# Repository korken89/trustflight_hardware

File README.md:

# ThrustFlight hardware reference design

A small and simple flight controller to be used with the  [trustflight firmware](https://github.com/korken89/trustflight_firmware) flight controller firmware, which is focusing on safety by using the Rust programming language.

## License

The hardware is OSHW using the Cern-OHL license.

## Images

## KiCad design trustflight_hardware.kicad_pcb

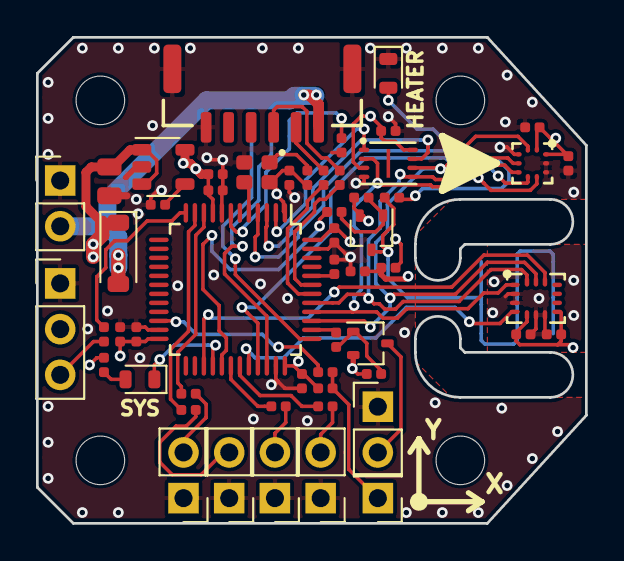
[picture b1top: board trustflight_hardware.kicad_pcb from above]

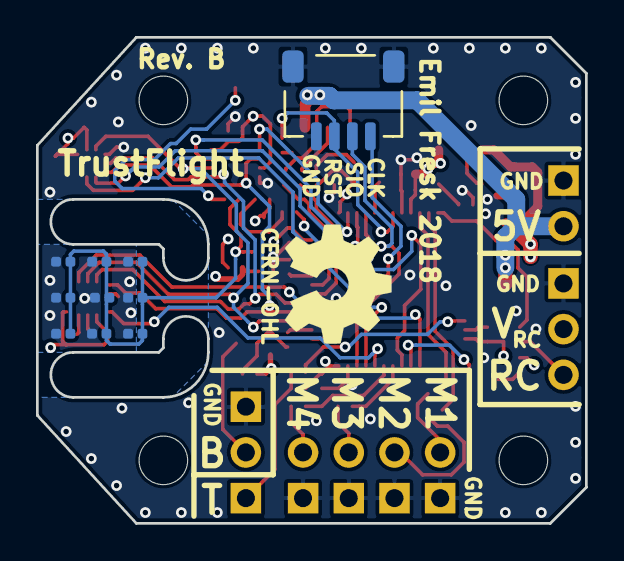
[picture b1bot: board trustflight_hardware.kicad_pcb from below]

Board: 4 copper layers, 30.5 x 27.0 mm, 69 parts (11 on the bottom side), 46 nets.

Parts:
C1, C2, C3, C4, C5, C7, C10, C12, C13, C14, C15, C16: 100n; C_0402_1005Metric_Rounded
C6: 22u; C_0805
C8, C9, C11: 4.7u; C_0402_1005Metric_Rounded
D1: LED_RED; D_0603_1608Metric_Rounded
D2: PMEG4005EGWX; D_SOD-123
D3: LED_BLUE; D_0603_1608Metric_Rounded
J1, J2, J3, J4, J6, J7: Conn_01x02; PinHeader_1x02_P2.54mm_Vertical
J5: Conn_01x01; PinHeader_1x01_P2.54mm_Vertical
J8: Conn_01x03; PinHeader_1x03_P2.54mm_Vertical
J9: swd-4; jst-sh-hor-4
J10: Dronecode_Telemetry; SM06B-GHS-TB
L1: MAF1005GAD352AT000; R_0402_1005Metric_Rounded
LOGO1: Logo_Open_Hardware_Small; OSHW-Symbol_6.7x6mm_SilkScreen
MK1, MK2, MK3, MK4: Mounting_Hole; MountingHole_2.7mm_M2.5
Q1, Q2: DMG1013UW; SOT-323_SC-70
R1, R2, R3, R4, R5, R12, R19, R21, R22, R23: 100; R_0402_1005Metric_Rounded
R6, R11: 1k; R_0402_1005Metric_Rounded
R7, R20, R24, R26: 10k; R_0402_1005Metric_Rounded
R8, R9, R10, R13, R14, R15, R16, R17, R18, R25: 180; R_0402_1005Metric_Rounded
U1: W25X40CLUXIG; USON-8-3x2mm-EP
U2: ISM330DLC; LGA-14-2.5x3
U3: BMP388; HLGA-10L-2.0x2.0-BMP388
U4: STM32F302CBT6; LQFP-48_7x7mm_Pitch0.5mm
U5: MIC5318-3.3YD5; SOT-23-5
X1: SIT8008BI-71-33S-16.000000G; Crystal_4Pin_2.0x1.6mm

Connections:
+3V3: C5.1, C9.1, C10.2, C11.1, C12.1, C13.1, C14.1, C16.1, L1.2, R11.2, R24.1, U1.3, U1.8, U4.1, U4.9, U4.24, U4.36, U4.48, U5.5, X1.4
+5V: D2.2, J6.2, J10.1
/BAR_CS: U3.6, U4.4
/BAR_INT: U3.7, U4.33
/BOOT0: R26.1, U4.44
/BUZZER: R23.2, U4.38
/BUZZ_P: J7.2, Q2.3
/CLK: U4.5, X1.3
/COM_RX: R22.2, U4.43
/COM_TX: R21.2, U4.42
/ESC_TLM: R12.2, U4.22
/ESC_TLM_P: J5.1, R11.1, R12.1
/F.port: R19.2, U4.12
/F.port_P: J8.3, R19.1
/FLASH_CS: U1.1, U4.2
/FLASH_HOLD: U1.7, U4.3
/HEATER: R1.2, U4.29
/IMU_CS: U2.12, U4.27
/IMU_INT: U2.4, U4.32
/LED: D3.1, U4.28
/M1: R2.2, U4.10
/M1_P: J1.2, R2.1
/M2: R3.2, U4.11
/M2_P: J2.2, R3.1
/M3: R4.2, U4.30
/M3_P: J3.2, R4.1
/M4: R5.2, U4.31
/M4_P: J4.2, R5.1
/MISO: U1.2, U2.1, U3.5, U4.40
/MOSI: U1.5, U2.14, U3.4, U4.41
/NRST: C15.2, J9.3, U4.7
/SCK: U1.6, U2.13, U3.2, U4.39
/SWCLK: J9.1, U4.37
/SWDIO: J9.2, U4.34
/VSYS: C6.1, D2.1, J8.2, Q1.2, Q2.2, R7.2, R20.2, R25.2, U5.1, U5.3
/V_HEAT: Q1.3, R6.1, R8.1, R9.1, R10.1, R13.1, R14.1, R15.1, R16.1, R17.1, R18.1
GND: C1.2, C2.2, C3.2, C4.2, C5.2, C6.2, C7.2, C8.2, C9.2, C10.1, C11.2, C12.2, C13.2, C14.2, C15.1, C16.2, D1.1, J1.1, J2.1, J3.1, J4.1, J6.1, J7.1, J8.1, J9.0, J9.4, J10.0, J10.6, R8.2, R9.2, R10.2, R13.2, R14.2, R15.2, R16.2, R17.2, R18.2, R26.2, U1.4, U2.2, U2.3, U2.6, U2.7, U3.3, U3.8, U3.9, U4.8, U4.23, U4.35, U4.47, U5.2, X1.2
unnamed: C7.1, U5.4
unnamed: D1.2, R6.2
unnamed: D3.2, R25.1
unnamed: J10.2, R21.1
unnamed: J10.3, R22.1
unnamed: Q1.1, R1.1, R7.1
unnamed: Q2.1, R20.1, R23.1
unnamed: R24.2, X1.1
VAA: C1.1, C2.1, C3.1, C4.1, C8.1, L1.1, U2.5, U2.8, U3.1, U3.10

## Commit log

2018-05-31 Most schematic done
2018-06-03 Most of schematic done, started pcb
2018-06-04 All components on PCB, almost ready for routing
2018-06-04 Fixed VSYS
2018-06-06 Most of PCB routing is done
2018-06-07 No DRC errors, all routed
2018-06-07 Added silkscreen and some finishing touches
2018-06-07 More additions
2018-06-11 Updated values, shrunk copper planes under IMU
2018-06-19 Added README
2018-06-21 Updated images
2018-06-25 Updated silkscreen
2018-07-21 Rev. B, fixed non 5V tolerant pins for heater/buzzer
2018-07-21 Added schematic plots
2018-11-03 Fixes for new KiCAD version and minor update to kicad_libs
